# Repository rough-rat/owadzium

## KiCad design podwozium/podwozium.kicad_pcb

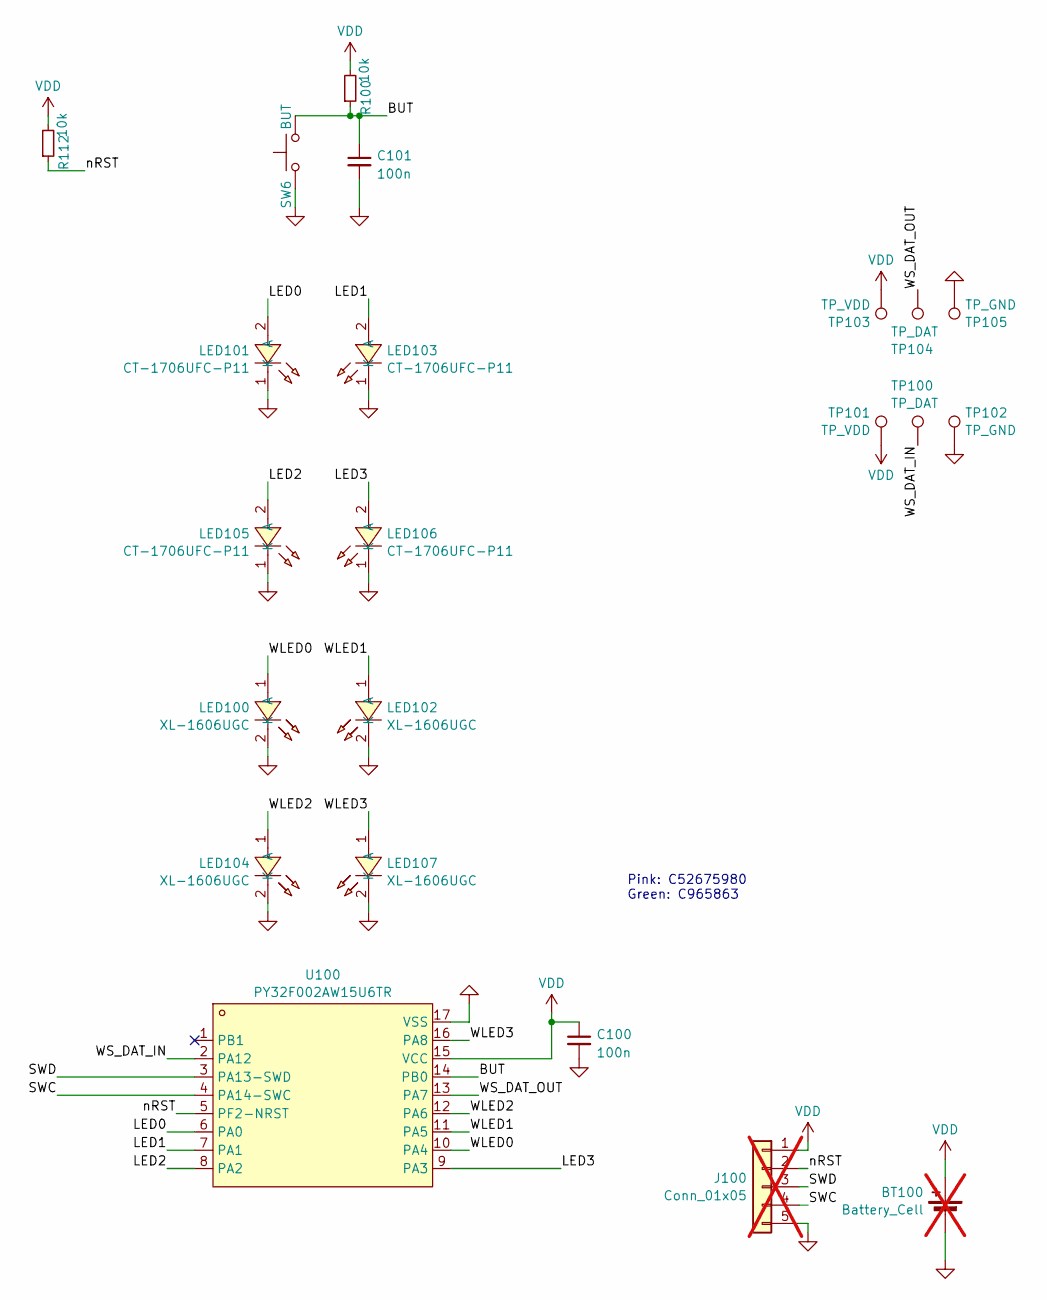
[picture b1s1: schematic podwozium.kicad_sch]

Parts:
BT100: Battery_Cell; BatteryHolder_Keystone_1060_1x2032; LCSC DNP; not fitted
C100, C101: 100n; C_0402_1005Metric; LCSC C1525
J100: Conn_01x05; PinHeader_1x05_P1.27mm_Vertical; LCSC DNP; not fitted
LED100, LED102, LED104, LED107: XL-1606UGC; LED-SMD_L1.7-W1.1-R-RD_GREEN; LCSC C965863
LED101, LED103, LED105, LED106: CT-1706UFC-P11; LED-SMD_L1.7-W1.1-RD_RED; MPN CT-1706UFC-P11; LCSC C52675980
R100, R112: 10k; R_0402_1005Metric; LCSC C25744
SW6: BUT; SW_SPST_TL3342; LCSC C7470214
TP100, TP104: TP_DAT; TestPoint_Pad_1.0x1.0mm
TP101, TP103: TP_VDD; TestPoint_Pad_1.0x1.0mm
TP102, TP105: TP_GND; TestPoint_Pad_1.0x1.0mm
U100: PY32F002AW15U6TR; TQFN-16_L3.0-W3.0-P0.50-BL-EP1.7; LCSC C5291740

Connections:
/BUT: C101.1, R100.1, SW6.1, U100.14 (PB0)
/LED0: LED101.2 (A), U100.6 (PA0)
/LED1: LED103.2 (A), U100.7 (PA1)
/LED2: LED105.2 (A), U100.8 (PA2)
/LED3: LED106.2 (A), U100.9 (PA3)
/SWC: J100.4, U100.4 (PA14-SWC)
/SWD: J100.3, U100.3 (PA13-SWD)
/WLED0: LED100.1 (A), U100.10 (PA4)
/WLED1: LED102.1 (A), U100.11 (PA5)
/WLED2: LED104.1 (A), U100.12 (PA6)
/WLED3: LED107.1 (A), U100.16 (PA8)
/WS_DAT_IN: TP100.1 (1_1), U100.2 (PA12)
/WS_DAT_OUT: TP104.1 (1_1), U100.13 (PA7)
/nRST: J100.2, R112.1, U100.5 (PF2-NRST)
GND: BT100.2 (-), C100.2, C101.2, J100.5, LED100.2 (K), LED101.1 (K), LED102.2 (K), LED103.1 (K), LED104.2 (K), LED105.1 (K), LED106.1 (K), LED107.2 (K), SW6.2, TP102.1 (1_1), TP105.1 (1_1), U100.17 (VSS)
VDD: BT100.1 (+), C100.1, J100.1, R100.2, R112.2, TP101.1 (1_1), TP103.1 (1_1), U100.15 (VCC)

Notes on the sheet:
Pink: C52675980 Green: C965863

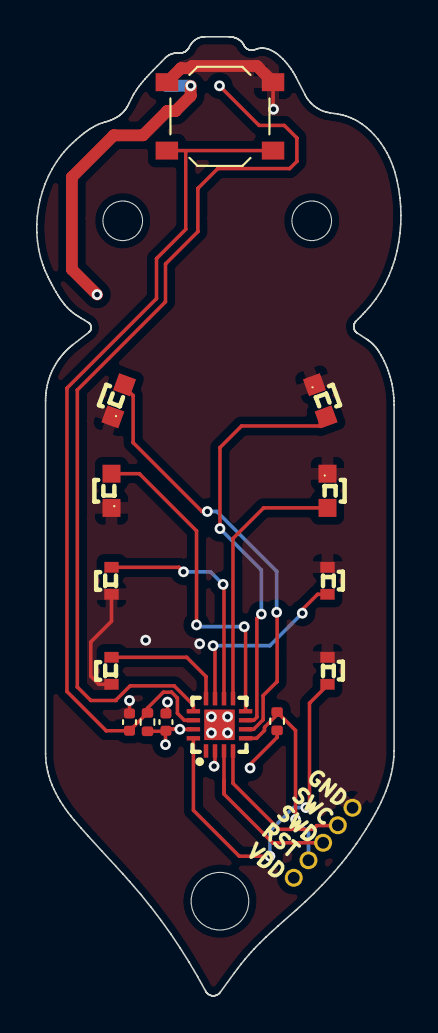
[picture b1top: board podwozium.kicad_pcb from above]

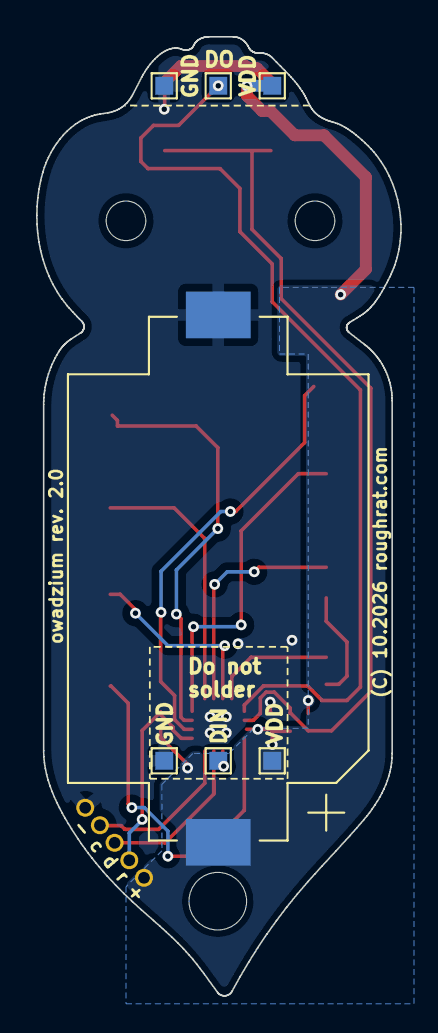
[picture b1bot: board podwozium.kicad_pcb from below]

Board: 2 copper layers, 20.2 x 53.3 mm, 22 parts (7 on the bottom side), 16 nets.

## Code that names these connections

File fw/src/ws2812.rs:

#![no_std]
#![no_main]

use cortex_m::peripheral::syst::SystClkSource;
use cortex_m_rt::entry;
use py32_hal::gpio::{Input, Level, Output, Pull, Speed};
use py32_hal::{pac, rcc::Sysclk, time::Hertz};
use {defmt_rtt as _, panic_halt as _};

mod ws2812_decode;
use ws2812_decode::packed_brightness;

core::arch::global_asm!(include_str!("ws2812_rx.s"), options(raw));
core::arch::global_asm!(include_str!("ws2812_tx.s"), options(raw));
extern "C" {
    fn ws2812_capture(bytes: *mut u8, idr: *const u32, capacity: u32) -> u32;
    fn ws2812_forward(bytes: *const u8, length: u32, timer: *mut ()) -> ();
}

const CLOCK: u32 = 24_000_000;
const LED_PINS: [u8; 8] = [4, 6, 5, 8, 0, 2, 1, 3];
const LED_MASK: u32 = 0x17f;
const RESET_TICKS: u32 = CLOCK / 1_000_000 * 50;
const LOCAL_BYTES: usize = 8 * 3;
const MAX_FRAME_BYTES: usize = 128 * 3;

// Read over SWD without stopping reception: frames, incomplete captures,
// enabled flag, eight latched brightness values, input and forwarded byte counts.
#[no_mangle]
static mut WS2812_STATUS: [u32; 13] = [0; 13];

fn status(index: usize, value: u32) {
    unsafe {
        core::ptr::addr_of_mut!(WS2812_STATUS)
            .cast::<u32>()
            .add(index)
            .write_volatile(value)
    }
}

fn elapsed(now: u32, before: u32) -> u32 {
    before.wrapping_sub(now) & 0x00ff_ffff
}

#[entry]
fn main() -> ! {
    let mut cfg = py32_hal::Config::default();
    cfg.rcc.hsi = Some(Hertz(CLOCK));
    cfg.rcc.sys = Sysclk::HSI;
    let p = py32_hal::init(cfg);
    // No interrupts or Embassy executor: reception and PWM share a polling loop.
    cortex_m::interrupt::disable();
    let _input = Input::new(p.PA12, Pull::Down);
    let _output = Output::new(p.PA7, Level::Low, Speed::VeryHigh);
    // PA7 AF2 = TIM1_CH1N. PWM1 plus inverted complementary polarity gives
    // positive pulses. CCR1 preload lets the CPU feed one bit ahead.
    py32_hal::rcc::enable_and_reset::<py32_hal::peripherals::TIM1>();
    let tim = pac::TIM1;
    tim.psc().write_value(0);
    tim.arr().write_value(pac::timer::regs::ArrCore(29));
    tim.ccr(0).write(|w| w.set_ccr(0));
    tim.ccmr_output(0).write(|w| {
        w.set_ocm(0, pac::timer::vals::Ocm::PWMMODE1);
        w.set_ocpe(0, true);
    });
    tim.ccer().write(|w| {
        w.set_ccne(0, true);
        w.set_ccnp(0, true);
    });
    tim.bdtr().write(|w| w.set_moe(true));
    tim.egr().write(|w| w.set_ug(true));
    tim.sr().write(|_| {});
    pac::GPIOA.afr(0).modify(|w| w.set_afr(7, 2));
    pac::GPIOA
        .moder()
        .modify(|w| w.set_moder(7, pac::gpio::vals::Moder::ALTERNATE));
    tim.cr1().write(|w| w.set_cen(true));
    let button = Input::new(p.PB0, Pull::None);
    let _leds = (
        Output::new(p.PA0, Level::Low, Speed::Low),
        Output::new(p.PA1, Level::Low, Speed::Low),
        Output::new(p.PA2, Level::Low, Speed::Low),
        Output::new(p.PA3, Level::Low, Speed::Low),
        Output::new(p.PA4, Level::Low, Speed::Low),
        Output::new(p.PA5, Level::Low, Speed::Low),
        Output::new(p.PA6, Level::Low, Speed::Low),
        Output::new(p.PA8, Level::Low, Speed::Low),
    );
    let mut core = cortex_m::Peripherals::take().unwrap();
    core.SYST.set_clock_source(SystClkSource::Core);
    core.SYST.set_reload(0x00ff_ffff);
    core.SYST.clear_current();
    core.SYST.enable_counter();
    let mut bytes = [0u8; MAX_FRAME_BYTES];
    let mut values = [0u8; 8];
    let mut pending = false;
    let mut captured = 0usize;
    let mut receiving = false;
    let mut low_since = None;
    let mut enabled = true;
    let mut button_raw = button.is_low();
    let mut button_stable = button_raw;
    let mut button_since = cortex_m::peripheral::SYST::get_current();
    let mut pwm_since = button_since;
    let mut accumulators = [0u16; 8];
    let mut frames = 0u32;
    let mut rejected = 0u32;
    status(2, 1);

    loop {
        let now = cortex_m::peripheral::SYST::get_current();
        let low = pac::GPIOA.idr().read().0 & (1 << 12) == 0;
        if low {
            let since = *low_since.get_or_insert(now);
            if elapsed(now, since) >= RESET_TICKS {
                if pending {
                    values = packed_brightness(&bytes[..LOCAL_BYTES]);
                    frames = frames.wrapping_add(1);
                    status(0, frames);
                    for i in 0..8 {
                        status(i + 3, values[i] as u32);
                    }
                    pending = false;
                    // The local eight pixels are consumed; retain the GRB byte
                    // order and values of every following pixel unchanged.
                    let tail = &bytes[LOCAL_BYTES..captured];
                    pac::GPIOA.brr().write_value(pac::gpio::regs::Brr(LED_MASK));
                    unsafe {
                        ws2812_forward(tail.as_ptr(), tail.len() as u32, tim.as_ptr().cast())
                    };
                    status(11, captured as u32);
                    status(12, tail.len() as u32);
                    low_since = None;
                }
                receiving = true;
            }
        } else {
            low_since = None;
        }

        let pressed = button.is_low();
        if pressed != button_raw {
            button_raw = pressed;
            button_since = now;
        }
        if pressed != button_stable && elapsed(now, button_since) >= CLOCK / 25 {
            button_stable = pressed;
            if pressed {
                enabled = !enabled;
                status(2, enabled as u32);
                if !enabled {
                    pac::GPIOA.brr().write_value(pac::gpio::regs::Brr(LED_MASK));
                }
            }
        }

        // Pulse-density modulation, capped at 25% duty because the board has
        // no LED series resistors. Capture blanks LEDs when data begins.
        if elapsed(now, pwm_since) >= CLOCK / 10_000 {
            pwm_since = now;
            let mut on = 0;
            for i in 0..8 {
                accumulators[i] += if enabled { values[i] as u16 } else { 0 };
                if accumulators[i] >= 1024 {
                    accumulators[i] -= 1024;
                    on |= 1 << LED_PINS[i];
                }
            }
            pac::GPIOA
                .bsrr()
                .write_value(pac::gpio::regs::Bsrr(on | ((LED_MASK & !on) << 16)));
        }

        if receiving {
            // The routine itself waits for the first edge, avoiding Rust entry
            // latency on bit zero. Idle calls return after about 85 us.
            let count = unsafe {
                ws2812_capture(
                    bytes.as_mut_ptr(),
                    pac::GPIOA.idr().as_ptr().cast(),
                    MAX_FRAME_BYTES as u32,
                )
            };
            if count != 0 {
                pending = count >= LOCAL_BYTES as u32
                    && count <= MAX_FRAME_BYTES as u32
                    && count % 3 == 0;
                captured = if pending { count as usize } else { 0 };
                if !pending {
                    rejected = rejected.wrapping_add(1);
                    status(1, rejected);
                }
                receiving = false;
                low_since = None;
            }
        }
    }
}
